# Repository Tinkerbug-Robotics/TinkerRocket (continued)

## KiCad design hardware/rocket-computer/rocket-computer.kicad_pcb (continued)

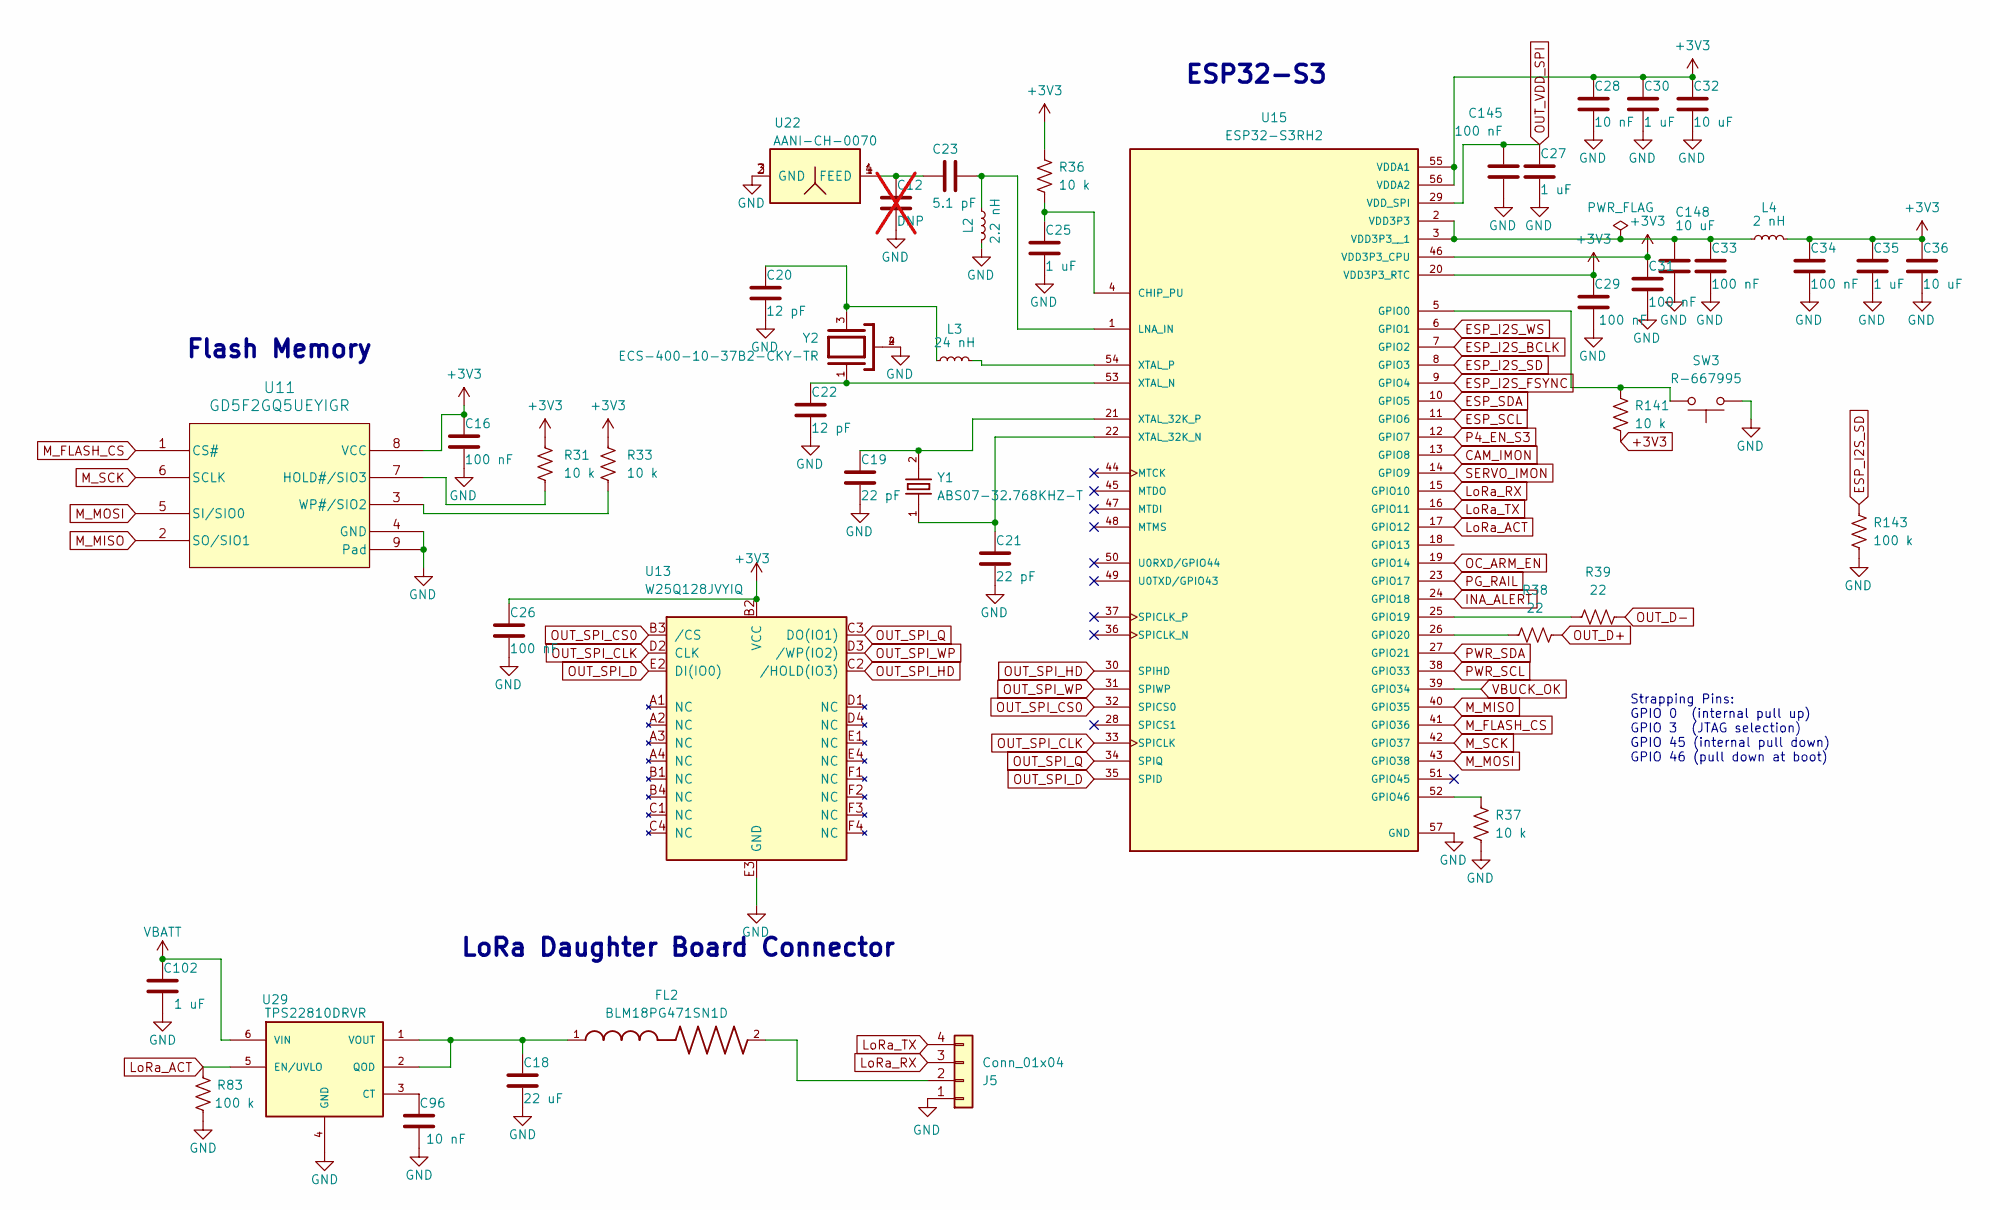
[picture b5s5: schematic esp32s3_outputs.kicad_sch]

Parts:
C12: DNP; C_0402_1005Metric; not fitted
C16, C26, C29, C31, C33, C34, C145: 100 nF; C_0402_1005Metric; MPN CL05B104KO5NNNC
C18: 22 uF; C_0805_2012Metric; MPN CL21A226MOQNNNE
C19, C21: 22 pF; C_0402_1005Metric; MPN CL05C220JB5NNNC
C20, C22: 12 pF; C_0402_1005Metric; MPN CL05C120JB5NNNC
C23: 5.1 pF; C_0402_1005Metric; MPN GJM1555C1H5R1WB01
C25, C27, C30, C35, C102: 1 uF; C_0402_1005Metric; MPN CL05A105KO5NNNC
C28, C96: 10 nF; C_0402_1005Metric; MPN CL05B103KB5NNNC
C32, C36, C148: 10 uF; C_0402_1005Metric; MPN CL05A106MQ5NUNC
FL2: BLM18PG471SN1D; BEADC1608X95N; MPN BLM18PG471SN1D
J5: Conn_01x04; JST_SH_BM04B-SRSS-TB_1x04-1MP_P1.00mm_Vertical; MPN BM04B-SRSS-TB
L2: 2.2 nH; L_0402_1005Metric; MPN LQW15AN2N2C10
L3: 24 nH; L_0402_1005Metric; MPN LQW15AN24NH00D
L4: 2 nH; L_0402_1005Metric; MPN LQG15HS2N0S02D
R31, R33, R36, R37, R141: 10 k; R_0402_1005Metric; MPN RC0402FR-0710KL
R38, R39: 22; R_0402_1005Metric; MPN RC0402FR-0722RL
R83, R143: 100 k; R_0402_1005Metric; MPN RC0402FR-07100KL
SW3: R-667995; R-667995_MIT; MPN R-667995
U11: GD5F2GQ5UEYIGR; 8L_WSON_8x6x3p4x4p3_MAC; MPN GD5F2GQ5UEYIGR
U13: W25Q128JVYIQ; 24-WLCSP_Y_WIN; MPN W25Q128JVYIQ
U15: ESP32-S3RH2; IC_ESP32-S3; PARTREV v1.2
U22: AANI-CH-0070; ANT_AANI-CH-0070_ABR; MPN AANI-CH-0070
U29: TPS22810DRVR; SON65P200X200X80-7N; MPN TPS22810DRVR
Y1: ABS07-32.768KHZ-T; XTAL_SC-32S_3215; MPN ABS07-32.768KHZ-T
Y2: ECS-400-10-37B2-CKY-TR; XTAL_ECS-400-10-37B2-CKY-TR; PARTREV 2021

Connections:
+3V3: C16.1, C26.1, C28.1, C29.1, C30.1, C31.1, C32.1, C34.1, C35.1, C36.1, L4.2, R31.2, R33.2, R36.1, R141.2, U11.8 (VCC), U13.B2 (VCC), U15.20 (VDD3P3_RTC), U15.46 (VDD3P3_CPU), U15.55 (VDDA1), U15.56 (VDDA2); also elsewhere on the board
CAM_IMON: U15.13 (GPIO8); also elsewhere on the board
ESP_I2S_BCLK: U15.7 (GPIO2); also elsewhere on the board
ESP_I2S_FSYNC: U15.9 (GPIO4); also elsewhere on the board
ESP_I2S_SD: R143.1, U15.8 (GPIO3); also elsewhere on the board
ESP_I2S_WS: U15.6 (GPIO1); also elsewhere on the board
ESP_SCL: U15.11 (GPIO6); also elsewhere on the board
ESP_SDA: U15.10 (GPIO5); also elsewhere on the board
GND: C12.2, C16.2, C18.2, C19.2, C20.2, C21.2, C22.2, C25.2, C26.2, C27.2, C28.2, C29.2, C30.2, C31.2, C32.2, C33.2, C34.2, C35.2, C36.2, C96.2, C102.2, C145.2, C148.2, J5.1, L2.2, R37.2, R83.2, R143.2, SW3.1, U11.4 (GND), U11.9 (Pad), U13.E3 (GND), U15.57 (GND), U22.2 (GND), U22.3 (GND), U29.4 (GND), U29.7 (GND), Y2.2, Y2.4; also elsewhere on the board
INA_ALERT: U15.24 (GPIO18); also elsewhere on the board
LoRa_ACT: R83.1, U15.17 (GPIO12), U29.5 (EN/UVLO)
LoRa_RX: J5.3, U15.15 (GPIO10)
LoRa_TX: J5.4, U15.16 (GPIO11)
M_FLASH_CS: U11.1 (CS#), U15.41 (GPIO36)
M_MISO: U11.2 (SO/SIO1), U15.40 (GPIO35)
M_MOSI: U11.5 (SI/SIO0), U15.43 (GPIO38)
M_SCK: U11.6 (SCLK), U15.42 (GPIO37)
unnamed: C12.1, C23.1, U22.1 (FEED), U22.4 (FEED)
unnamed: C20.1, L3.1, Y2.3
unnamed: FL2.2, J5.2
unnamed: R31.1, U11.7 (HOLD#/SIO3)
unnamed: R33.1, U11.3 (WP#/SIO2)
unnamed: C25.1, R36.2, U15.4 (CHIP_PU)
unnamed: R141.1, SW3.2, U15.5 (GPIO0)
unnamed: R39.2, U15.25 (GPIO19)
unnamed: R38.2, U15.26 (GPIO20)
unnamed: R37.1, U15.52 (GPIO46)
unnamed: C23.2, L2.1, U15.1 (LNA_IN)
unnamed: C33.1, C148.1, L4.1, U15.2 (VDD3P3), U15.3 (VDD3P3__1)
unnamed: C21.1, U15.22 (XTAL_32K_N), Y1.1
unnamed: C19.1, U15.21 (XTAL_32K_P), Y1.2
unnamed: C22.1, U15.53 (XTAL_N), Y2.1
unnamed: L3.2, U15.54 (XTAL_P)
unnamed: C96.1, U29.3 (CT)
unnamed: C18.1, FL2.1, U29.1 (VOUT), U29.2 (QOD)
OC_ARM_EN: U15.19 (GPIO14); also elsewhere on the board
OUT_D+: R38.1; also elsewhere on the board
OUT_D-: R39.1; also elsewhere on the board
OUT_SPI_CLK: U13.D2 (CLK), U15.33 (SPICLK)
OUT_SPI_CS0: U13.B3 (/CS), U15.32 (SPICS0)
OUT_SPI_D: U13.E2 (DI(IO0)), U15.35 (SPID)
OUT_SPI_HD: U13.C2 (/HOLD(IO3)), U15.30 (SPIHD)
OUT_SPI_Q: U13.C3 (DO(IO1)), U15.34 (SPIQ)
OUT_SPI_WP: U13.D3 (/WP(IO2)), U15.31 (SPIWP)
OUT_VDD_SPI: C27.1, C145.1, U15.29 (VDD_SPI)
P4_EN_S3: U15.12 (GPIO7); also elsewhere on the board
PG_RAIL: U15.23 (GPIO17); also elsewhere on the board
PWR_SCL: U15.38 (GPIO33); also elsewhere on the board
PWR_SDA: U15.27 (GPIO21); also elsewhere on the board
SERVO_IMON: U15.14 (GPIO9); also elsewhere on the board
VBATT: C102.1, U29.6 (VIN); also elsewhere on the board
VBUCK_OK: U15.39 (GPIO34); also elsewhere on the board

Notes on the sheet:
Strapping Pins: GPIO 0 (internal pull up) GPIO 3 (JTAG selection) GPIO 45 (internal pull down) GPIO 46 (pull down at boot)
ESP32-S3
Flash Memory
LoRa Daughter Board Connector

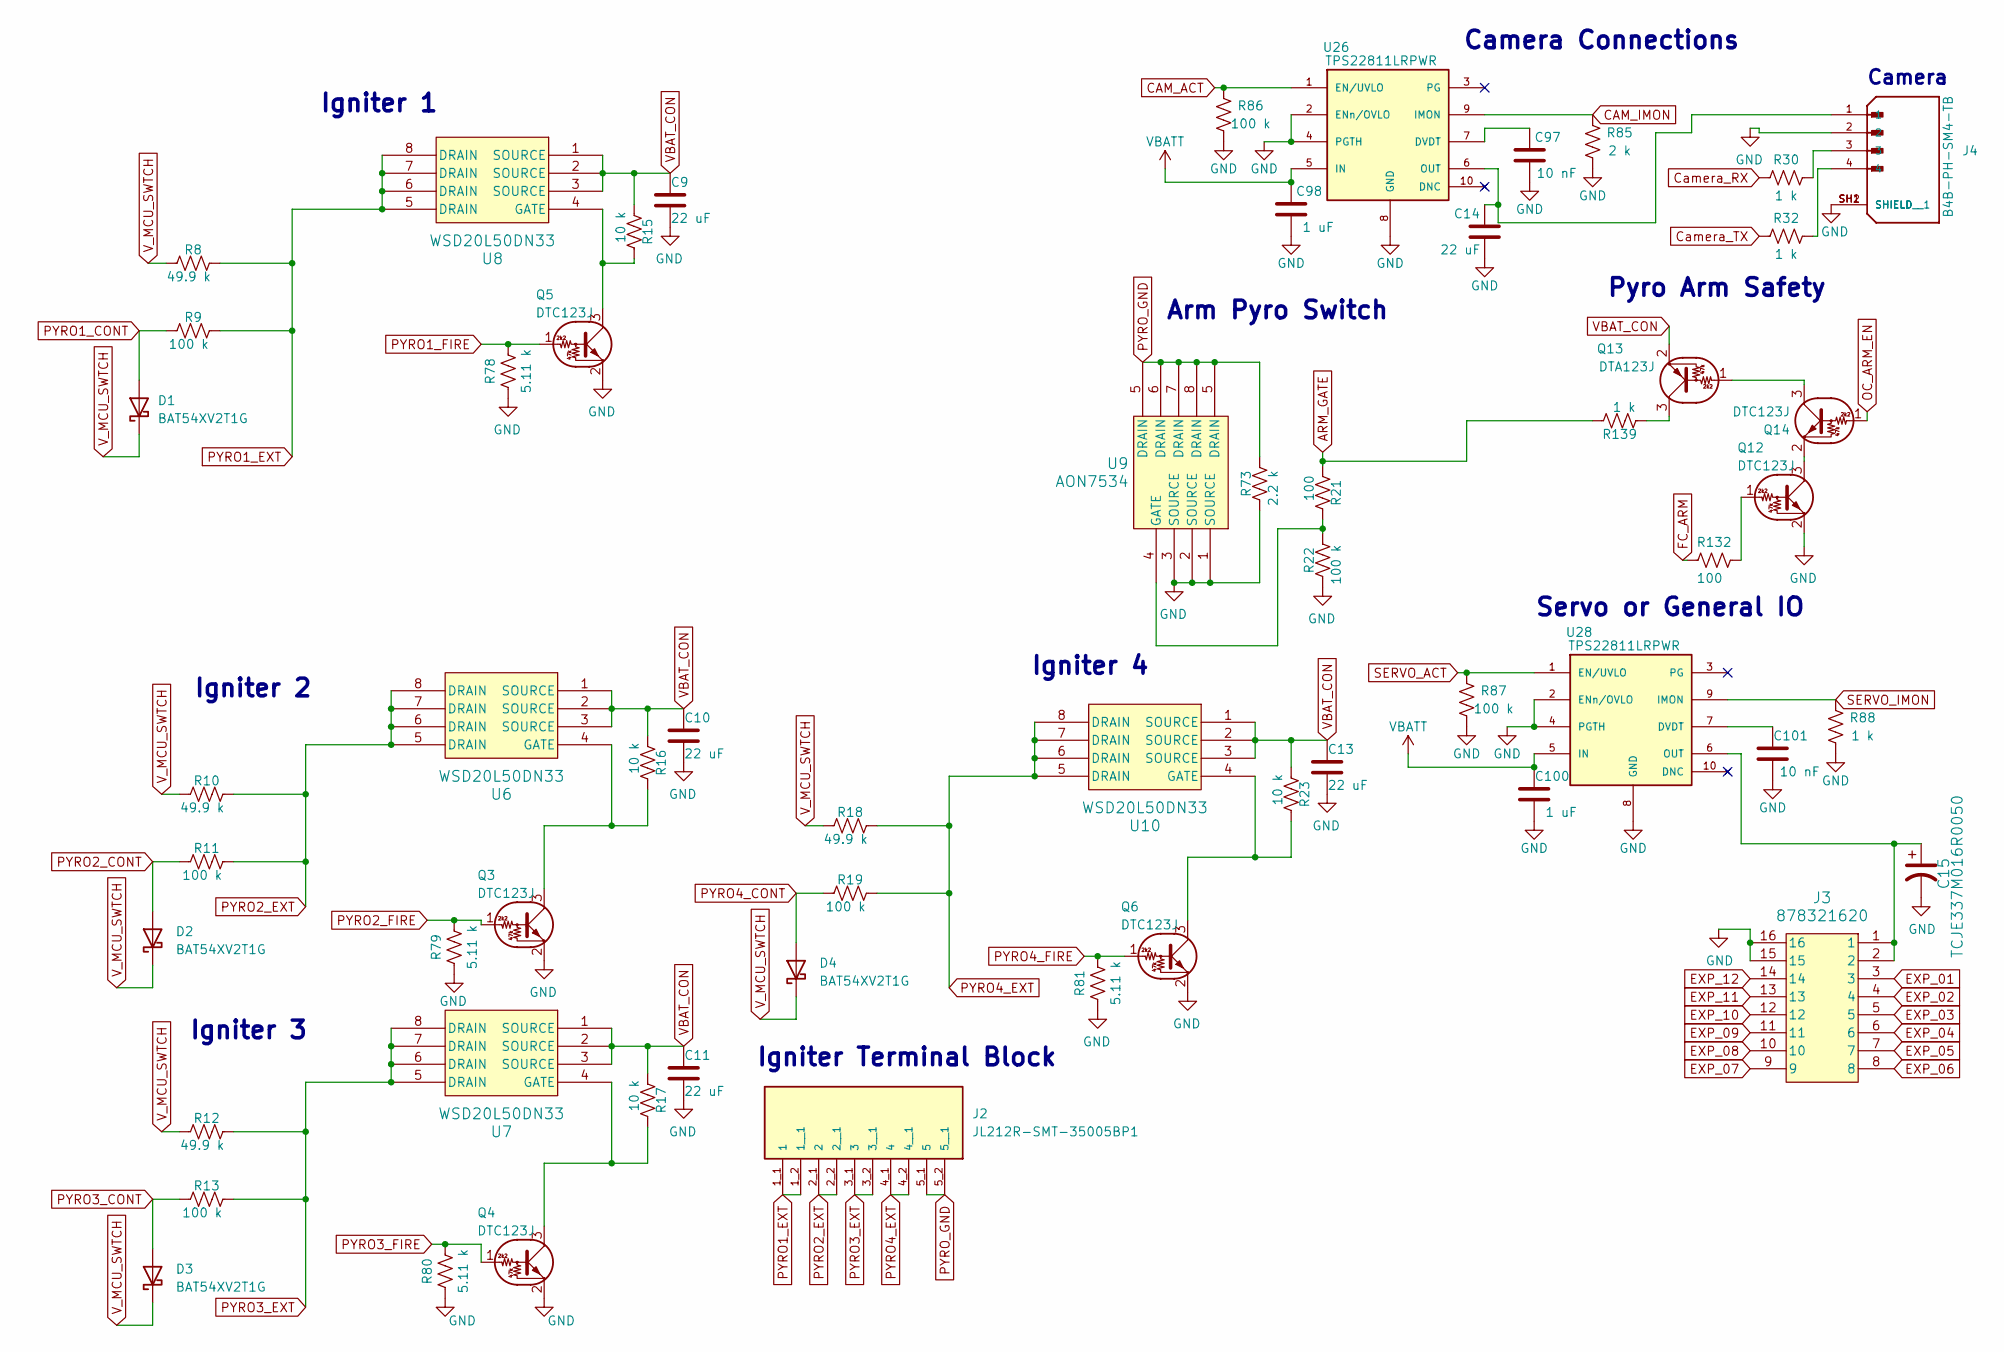
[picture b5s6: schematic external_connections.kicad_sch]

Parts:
C9, C10, C11, C13, C14: 22 uF; C_0805_2012Metric; MPN CL21A226MOQNNNE
C15: TCJE337M016R0050; CAPMP7.6X4.3_3.1N_KEM; MPN TCJE337M016R0050
C97, C101: 10 nF; C_0402_1005Metric; MPN CL05B103KB5NNNC
C98, C100: 1 uF; C_0402_1005Metric; MPN CL05A105KO5NNNC
D1, D2, D3, D4: BAT54XV2T1G; SOD-523_0P9X1P3_ONS; MPN BAT54XV2T1G
J2: JL212R-SMT-35005BP1; CUI_TBLH11-350-05-BK; PARTREV 1.0
J3: 878321620; CONN16_878321620_MOL; MPN 878321620
J4: B4B-PH-SM4-TB; JST_B4B-PH-SM4-TB; PARTREV N/A
Q3, Q4, Q5, Q6, Q12, Q14: DTC123J; TRANS_SOT-416_EMT3-EMT3F_ROHM; MPN DTC123JETL
Q13: DTA123J; TRANS_SOT-416_EMT3-EMT3F_ROHM; MPN DTA123JETL
R8, R10, R12, R18: 49.9 k; R_0402_1005Metric; MPN RC0402FR-0749K9L
R9, R11, R13, R19, R22, R86, R87: 100 k; R_0402_1005Metric; MPN RC0402FR-07100KL
R15, R16, R17, R23: 10 k; R_0402_1005Metric; MPN RC0402FR-0710KL
R21, R132: 100; R_0402_1005Metric; MPN RC0402FR-07100RL
R30, R32, R88, R139: 1 k; R_0402_1005Metric; MPN RC0402FR-071KL
R73: 2.2 k; R_0402_1005Metric; MPN RC0402FR-072K2L
R78, R79, R80, R81: 5.11 k; R_0402_1005Metric; MPN RC0402FR-075K11L
R85: 2 k; R_0402_1005Metric; MPN RC0402FR-072KL
U6, U7, U8, U10: WSD20L50DN33; TSON Advance_TOS; MPN WSD20L50DN33
U9: AON7534; TSON Advance_TOS; MPN AON7534
U26, U28: TPS22811LRPWR; IC_TPS22811LRPWR; MPN TPS22811LRPWR

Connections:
ARM_GATE: R21.2, R139.1
CAM_ACT: R86.1, U26.1 (EN/UVLO); also elsewhere on the board
CAM_IMON: R85.1, U26.9 (IMON); also elsewhere on the board
Camera_RX: R30.1; also elsewhere on the board
Camera_TX: R32.1; also elsewhere on the board
EXP_01: J3.3; also elsewhere on the board
EXP_02: J3.4; also elsewhere on the board
EXP_03: J3.5; also elsewhere on the board
EXP_04: J3.6; also elsewhere on the board
EXP_05: J3.7; also elsewhere on the board
EXP_06: J3.8; also elsewhere on the board
EXP_07: J3.9; also elsewhere on the board
EXP_08: J3.10; also elsewhere on the board
EXP_09: J3.11; also elsewhere on the board
EXP_10: J3.12; also elsewhere on the board
EXP_11: J3.13; also elsewhere on the board
EXP_12: J3.14; also elsewhere on the board
FC_ARM: R132.2; also elsewhere on the board
GND: C9.2, C10.2, C11.2, C13.2, C14.2, C15.2, C97.2, C98.2, C100.2, C101.2, J3.15, J3.16, J4.2, J4.SH1 (SHIELD), J4.SH2 (SHIELD__1), Q3.2 (E), Q4.2 (E), Q5.2 (E), Q6.2 (E), Q12.2 (E), R22.2, R73.2, R78.1, R79.1, R80.1, R81.1, R85.2, R86.2, R87.2, R88.2, U9.1 (SOURCE), U9.2 (SOURCE), U9.3 (SOURCE), U26.2 (ENn/OVLO), U26.4 (PGTH), U26.8 (GND), U28.2 (ENn/OVLO), U28.4 (PGTH), U28.8 (GND); also elsewhere on the board
unnamed: J4.3, R30.2
unnamed: J4.4, R32.2
unnamed: Q3.3 (C), R16.1, U6.4 (GATE)
unnamed: Q4.3 (C), R17.1, U7.4 (GATE)
unnamed: Q5.3 (C), R15.1, U8.4 (GATE)
unnamed: Q6.3 (C), R23.1, U10.4 (GATE)
unnamed: Q12.1 (B), R132.1
unnamed: Q12.3 (C), Q14.2 (E)
unnamed: Q13.1 (B), Q14.3 (C)
unnamed: Q13.3 (C), R139.2
unnamed: R21.1, R22.1, U9.4 (GATE)
unnamed: C97.1, U26.7 (DVDT)
unnamed: C14.1, J4.1, U26.6 (OUT)
unnamed: C101.1, U28.7 (DVDT)
unnamed: C15.1, J3.1, J3.2, U28.6 (OUT)
OC_ARM_EN: Q14.1 (B); also elsewhere on the board
PYRO1_CONT: D1.2 (A), R9.2; also elsewhere on the board
PYRO1_EXT: J2.1_1 (1), J2.1_2 (1__1), R8.1, R9.1, U8.5 (DRAIN), U8.6 (DRAIN), U8.7 (DRAIN), U8.8 (DRAIN)
PYRO1_FIRE: Q5.1 (B), R78.2; also elsewhere on the board
PYRO2_CONT: D2.2 (A), R11.2; also elsewhere on the board
PYRO2_EXT: J2.2_1 (2), J2.2_2 (2__1), R10.1, R11.1, U6.5 (DRAIN), U6.6 (DRAIN), U6.7 (DRAIN), U6.8 (DRAIN)
PYRO2_FIRE: Q3.1 (B), R79.2; also elsewhere on the board
PYRO3_CONT: D3.2 (A), R13.2; also elsewhere on the board
PYRO3_EXT: J2.3_1 (3), J2.3_2 (3__1), R12.1, R13.1, U7.5 (DRAIN), U7.6 (DRAIN), U7.7 (DRAIN), U7.8 (DRAIN)
PYRO3_FIRE: Q4.1 (B), R80.2; also elsewhere on the board
PYRO4_CONT: D4.2 (A), R19.2; also elsewhere on the board
PYRO4_EXT: J2.4_1 (4), J2.4_2 (4__1), R18.1, R19.1, U10.5 (DRAIN), U10.6 (DRAIN), U10.7 (DRAIN), U10.8 (DRAIN)
PYRO4_FIRE: Q6.1 (B), R81.2; also elsewhere on the board
PYRO_GND: J2.5_1 (5), J2.5_2 (5__1), R73.1, U9.5 (DRAIN), U9.6 (DRAIN), U9.7 (DRAIN), U9.8 (DRAIN)
SERVO_ACT: R87.1, U28.1 (EN/UVLO); also elsewhere on the board
SERVO_IMON: R88.1, U28.9 (IMON); also elsewhere on the board
VBATT: C98.1, C100.1, U26.5 (IN), U28.5 (IN); also elsewhere on the board
VBAT_CON: C9.1, C10.1, C11.1, C13.1, Q13.2 (E), R15.2, R16.2, R17.2, R23.2, U6.1 (SOURCE), U6.2 (SOURCE), U6.3 (SOURCE), U7.1 (SOURCE), U7.2 (SOURCE), U7.3 (SOURCE), U8.1 (SOURCE), U8.2 (SOURCE), U8.3 (SOURCE), U10.1 (SOURCE), U10.2 (SOURCE), U10.3 (SOURCE); also elsewhere on the board
V_MCU_SWTCH: D1.1 (K), D2.1 (K), D3.1 (K), D4.1 (K), R8.2, R10.2, R12.2, R18.2; also elsewhere on the board

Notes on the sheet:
Igniter Terminal Block
Camera
Servo or General IO
Igniter 1
Arm Pyro Switch
Igniter 2
Igniter 4
Pyro Arm Safety
Camera Connections
Igniter 3

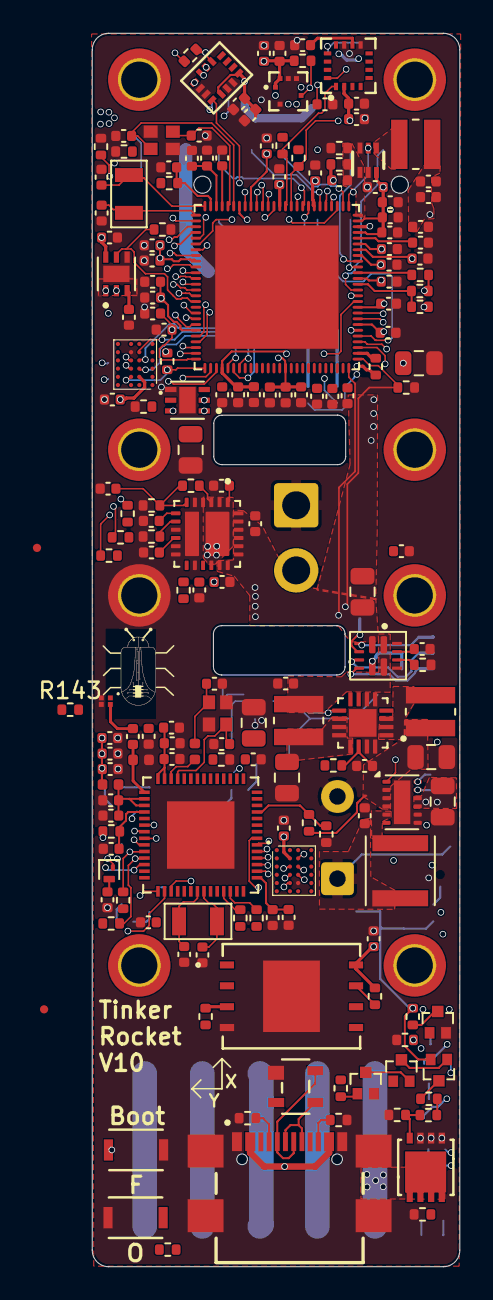
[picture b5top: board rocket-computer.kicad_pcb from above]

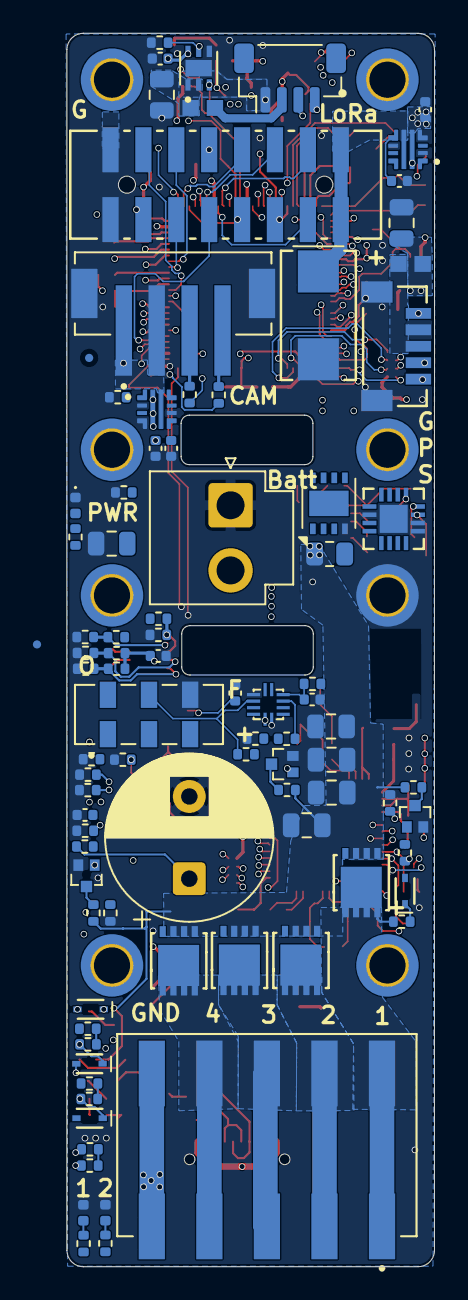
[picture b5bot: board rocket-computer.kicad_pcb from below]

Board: 8 copper layers, 22.3 x 75.0 mm, 276 parts (89 on the bottom side), 183 nets.
